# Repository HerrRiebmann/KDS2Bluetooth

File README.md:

# KDS2Bluetooth
Kawasaki Diagnostic Service Reader via Bluetooth

Using an Arduino (*Nano*) to read parameter from a Kawasaki motorcycle by it´s diagnostic system.
Requests can be submittet via bluetooth, by any ELM327 compatible device/application. Such as Android App [Torque Lite](https://play.google.com/store/apps/details?id=org.prowl.torque&hl=de), [Car Scanner ELM OBD2](https://play.google.com/store/apps/details?id=com.ovz.carscanner&hl=de), 
action cameras like "Garmin Virb X / XE" or other solutions, which are able to communicate with an OBD II Bluetooth Adapter.
For racetrack usage, I can recommend [Racechrono](https://racechrono.com/)

# Update 2023/01/01
My latest so called "Bike Diagnostic System" version for Kawasaki & Suzuki. It´s almost compatible to any ELM327 App and supports nearly any KDS and SDS bike.
It has tons of settings, parameter, modes and an error log.

### Repository
* [ECU Emulation](https://github.com/HerrRiebmann/KDS2Bluetooth/tree/master/ECU%20Emulation) - Visual Studio C# Project to emulate the ECU
* [Bike_Diagnostic_System](https://github.com/HerrRiebmann/KDS2Bluetooth/tree/master/Bike_Diagnostic_System)    - Arduino Sketch -> Full solution (new)
* [ECU_Reader](https://github.com/HerrRiebmann/KDS2Bluetooth/tree/master/ECU_Reader)    - Arduino Sketch -> Full solution (old)
* [HC06_Sniffer](https://github.com/HerrRiebmann/KDS2Bluetooth/tree/master/HC06_Sniffer)  - Arduino Sketch to find out Bluetooth AT-commands
* [Documentation](https://github.com/HerrRiebmann/KDS2Bluetooth/tree/master/Documentation) - OBD / KDS PID-List, Schematics, ect.

### History:
Against all cars and trucks, the diagnostic interface is not standardized on two wheels.
Neither the plug, nor the communication.
Since ~1996 ODB and later on OBD II interface entered nearly every car. The motorbike manufactures are cooking their very own soup.

That´s why I cannot use a cheap (*china*) OBD II to Bluetooth adapter, to transfer RPM, Speed, Temperatures, Throttle, ect.
to my Garmin Virb XE action cam.
Also my bike doesn´t have any gear indicator. So I´d like to build my very own.

### Protocol:
KDS Bus via K-LINE (*Diagnostic plug*).
In my case KWP2000 (*ISO-14230*)

### Hardware:
* Arduino Nano
* HC-06 Bluetooth
* L9637D
* Ceramic-Capacitor 10 nF 50 V/DC
* 510Ohm Resistor
* SOIC Board (*to solder L9637 SMD on it*)

The L9637 converts the one wire K-Line bidirectional into a serial signal (Rx & Tx).
Connect Rx to Rx, Tx to Tx and VCC to 5V Output from Arduino. VCC, Gnd and K-Line to the Bike. A PullUp-resistor is needed between power supply (VCC) and K-Line!
HC-06 is a slave Bluetooth device. If needed, you can use a HC-05 master.

### Software:
This has to be splitted into three parts:

#### AT-Communication:
Nearly all bluetooth OBD dongles are using an ELM327 chip, or a similar, cheap china clone.
This is controlled/setup via "AT"-commands. They describe the format how data is transmitted, timing, reset the device or return protocol information.

#### KDS-Communication:
Connection to the kawasaki diagnostic system. How the Arduino speaks to the Bike.
Based on the great work of Tom Mitchell (*[Kawaduino](https://bitbucket.org/tomnz/kawaduino/overview)*).

#### Translations:
Every ELM327 compatible device is using the stock [OBD II protocol](https://en.wikipedia.org/wiki/OBD-II_PIDs) and its Protocol ID´s (*PID*).
The bike is also using a similar communication. But the PID´s doesn´t mean the same, nor is the calcualtion equal.
In that conclusion, the requested PID has to be translated into the according pendant and the result has to be calculated,
to fit into the OBD ranges.

### The most influential Tutorials/sources:
[KDS Protocol](https://web.archive.org/web/20201202041417/https://ecuhacking.activeboard.com/t56234221/kds-protocol/) (inactive ecuhacking.activeboard via archive.org)

[Kawaduino](https://github.com/tomnz/kawaduino)

[ELM327 AT Commands](https://www.elmelectronics.com/wp-content/uploads/2016/07/ELM327DS.pdf)

[OBDuino](https://en.wikipedia.org/wiki/OBDuino)

### My Cameras:
[Garmin Virb XE](http://virb.garmin.com/en-US/virb-xe)
[Garmin Virb X](http://virb.garmin.com/en-US/virb-x)

### My Videos (*more to come*)

[My YouTube Channel](https://www.youtube.com/channel/UCT6vRSUNHg8XRwPQtbxhyKw)

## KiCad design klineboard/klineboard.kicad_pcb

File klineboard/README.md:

The pcb design is made by Kicad 5.1.5 which it can be download at
https://www.kicad-pcb.org/

This PCB follow the schematic which included in this project
*It's still in beta version, I will improve it : )*

Thanks for HerrRiebmann's work

Board overview

https://github.com/spcrxj/KDS2Bluetooth/blob/master/klineboard/board.png

https://github.com/spcrxj/KDS2Bluetooth/blob/master/klineboard/3d.png

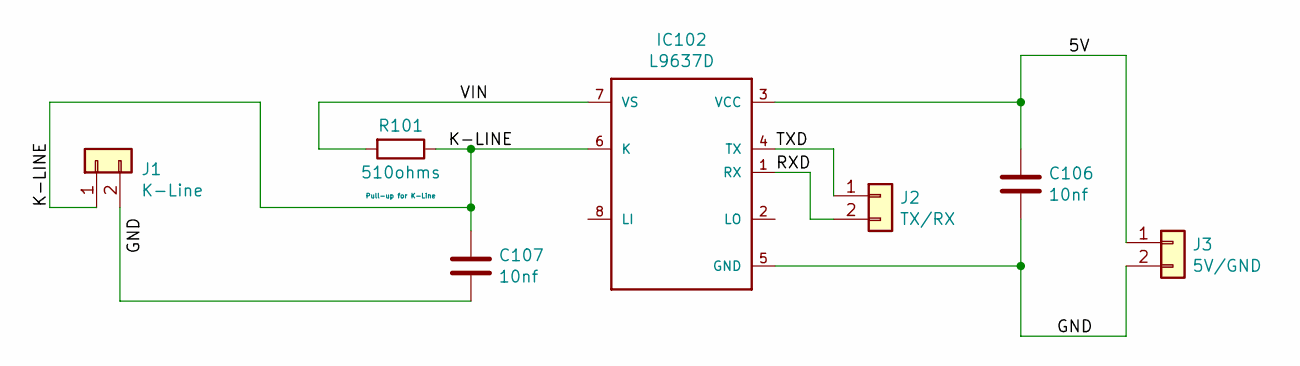
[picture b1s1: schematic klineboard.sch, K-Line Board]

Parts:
C106, C107: 10nf; C_0603_HandSoldering; digikey 490-GCM1885C1H100FA16DDKR-ND
IC102: L9637D; SO08; digikey 497-10483-2-ND
J1: K-Line; Pin_Header_Angled_1x02_Pitch2.54mm
J2: TX/RX; Pin_Header_Angled_1x02_Pitch2.54mm
J3: 5V/GND; Pin_Header_Angled_1x02_Pitch2.54mm
R101: 510ohms; R_0603_HandSoldering; digikey P123050TR-ND

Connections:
/5V: C106.1, IC102.3 (VCC), J3.1
/GND: C106.2, IC102.5 (GND), J3.2
/K-LINE: C107.1, IC102.6 (K), J1.1, R101.1
/RXD: IC102.1 (RX), J2.2
/TXD: IC102.4 (TX), J2.1
/VIN: IC102.7 (VS), R101.2
unnamed: C107.2, J1.2

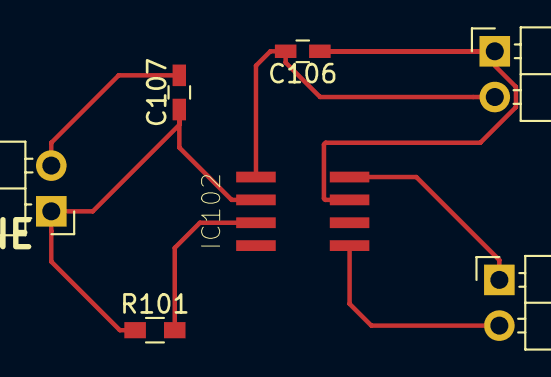
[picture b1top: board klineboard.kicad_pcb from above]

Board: 2 copper layers, 7 parts (0 on the bottom side), 7 nets.

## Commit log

2015-11-05 :octocat: Added .gitattributes & .gitignore files
2015-11-05 Initial Upload
2015-11-05 Initial Upload
    Arduino Projects
2015-11-05 Delete Debug & Release files
    Removed *.dll and *.exe files
2015-11-05 Initial Upload
    Documentation files:
    OBD<->KDS PID-List
    ELM327
    ISO-Protocol
    L9637 Scematic
2015-11-13 Throttle & Throttle Valve
    Throttle Calculation Updated
    Sniffer changed for testing
2015-11-13 Improve Calculation
    Improved calculation and valid value ranges in ECU Emulator.
    Optimized Intake & barometric pressure calculation in Arduino Sketch
    ECU_Reader
2015-11-21 Throttle > 100% Fix | LCD Support
    LCD Code included but commented. The according librarys are to big :(
    they had to be reduced first.
2015-12-31 Throttle max value
    Throttle maximal value is now dynamical and gets stored onto the EEPROM.
    Avoid some possible zero divisions.
2016-03-09 Sub Throttle valve Sensor
    Some optimizations and storing the max values to eeprom
2016-06-22 Improved calculations and stability
    Removed LCD
    Optimized Calculations
    Optimized Stability
    Added possibility to use diagnostic-features
    And much more...
2016-06-23 Bugfixing
    Some small corrections
2016-07-01 Updated ServiceCodes
2016-07-01 Initial Upload
    Screenshots
2016-07-01 Initial Upload
    Screenshot
2018-01-22 Cirquit Diagram L9637D
2019-10-15 New Hex Reader
2019-10-17 Updated Screenshot
2020-02-03 K-Line Board Design 1.0 Beta
    Added K-Line Board Design 1.0 Beta
2020-02-13 Create README.md
    Readme
2021-10-04 Create LICENSE
2022-06-22 Bump Newtonsoft.Json from 7.0.1 to 13.0.1 in /ECU Emulation/Backend
    Bumps [Newtonsoft.Json](https://github.com/JamesNK/Newtonsoft.Json) from 7.0.1 to 13.0.1.
    - [Release notes](https://github.com/JamesNK/Newtonsoft.Json/releases)
    - [Commits](https://github.com/JamesNK/Newtonsoft.Json/compare/7.0.1...13.0.1)
    ---
    updated-dependencies:
    - dependency-name: Newtonsoft.Json
2023-01-01 Update README.md
    Added new BDS code
2023-01-02 Update README.md
    Added Racechrono Link
2023-01-02 Initial upload
    Serial Bluetooth Terminal Screenshot
2023-01-02 New Hex Viewer and Bugfixes
2023-02-15 Trim whitespace
    Optimized string handling with spaces
2023-02-15 Add Graph
    Added the ability to show data on a graph
